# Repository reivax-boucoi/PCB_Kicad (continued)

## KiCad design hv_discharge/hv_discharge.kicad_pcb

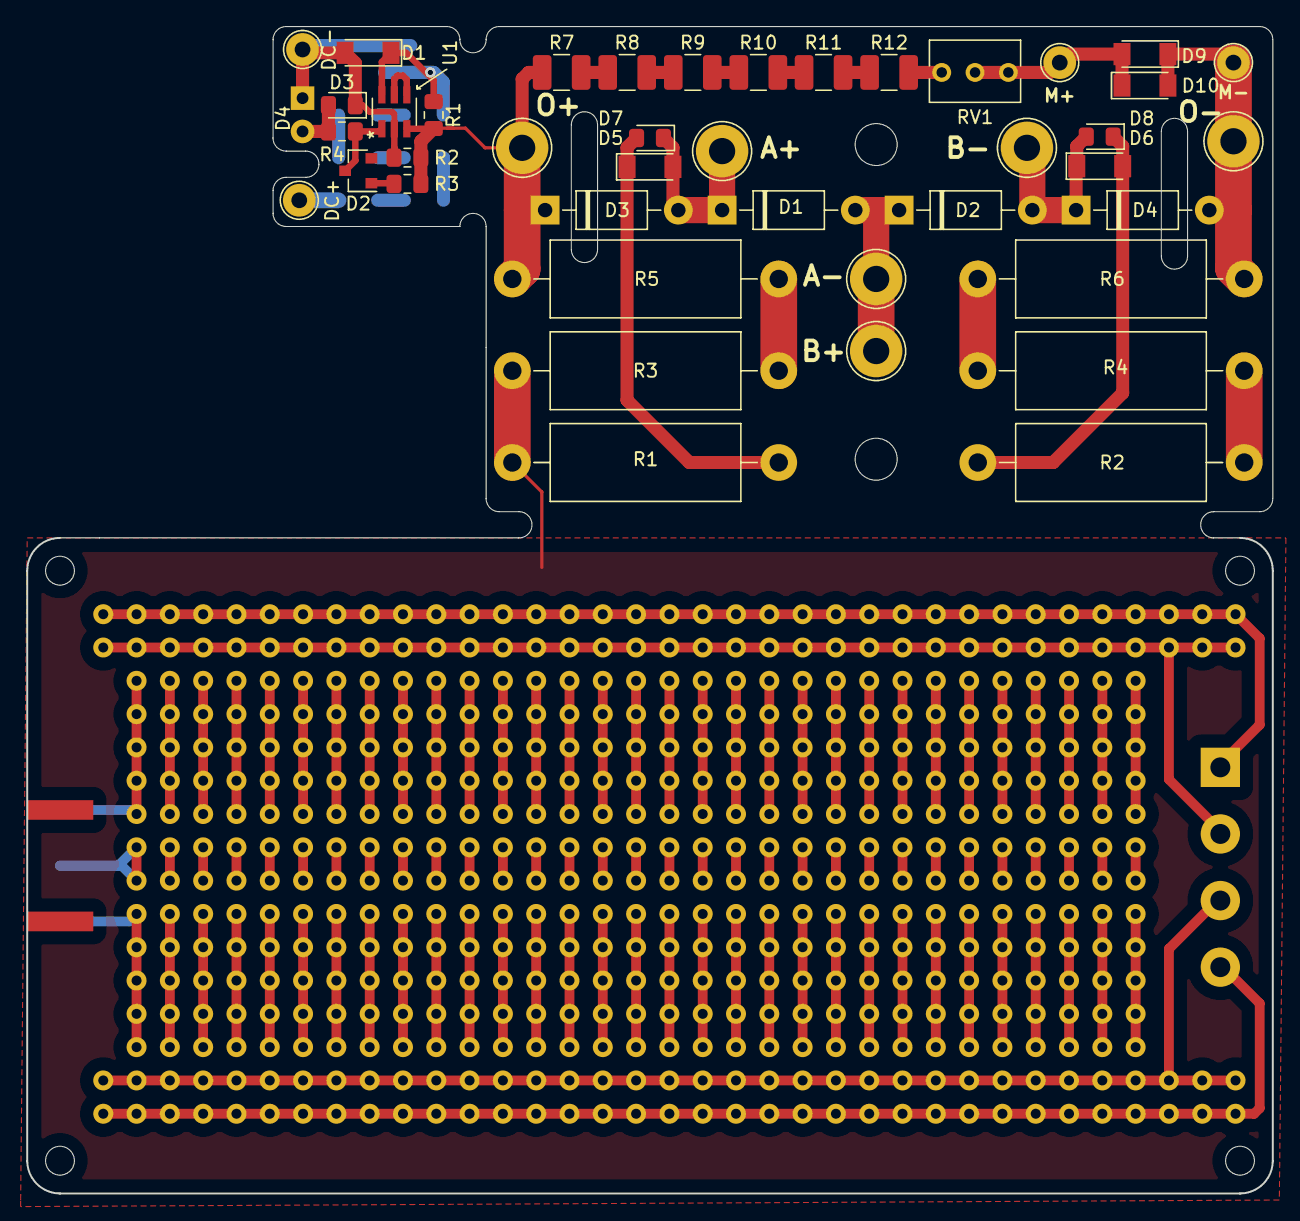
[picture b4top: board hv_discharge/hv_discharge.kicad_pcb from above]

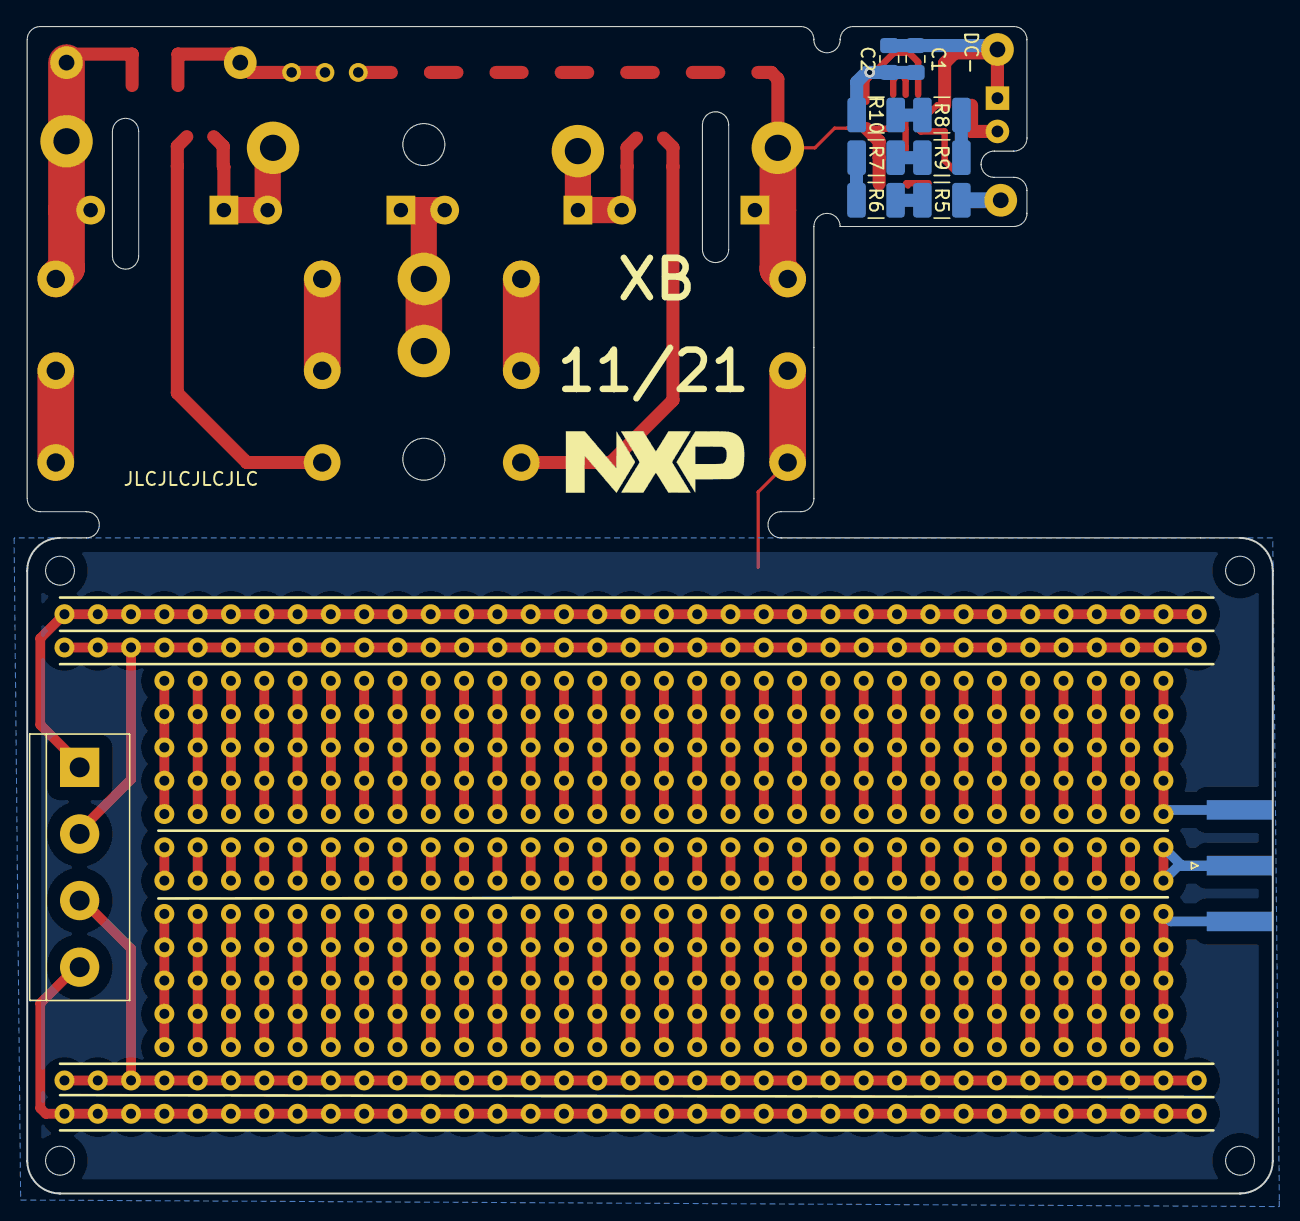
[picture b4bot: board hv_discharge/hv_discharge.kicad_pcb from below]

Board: 2 copper layers, 95.0 x 89.0 mm, 50 parts (8 on the bottom side), 18 nets.

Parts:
C1, C2: 10u; C_0805_2012Metric_Pad1.15x1.40mm_HandSolder
D1: D_Zener; D_MiniMELF
D1#2, D2#2, D3#2, D4#2: 1N4007; D_DO-41_SOD81_P10.16mm_Horizontal
D2: BAT54W; SOT-23
D3, D7, D8: LED; LED_0805_2012Metric_Pad1.15x1.40mm_HandSolder
D4: LED; LED_D5.0mm
D5, D6, D9, D10: D; D_MiniMELF
DC+: DC+; TestPoint_THTPad_D2.5mm_Drill1.2mm
DC-: DC-; TestPoint_THTPad_D2.5mm_Drill1.2mm
J1: B-; TestPoint_THTPad_D4.0mm_Drill2.0mm
J2: A+; TestPoint_THTPad_D4.0mm_Drill2.0mm
J3: B+; TestPoint_THTPad_D4.0mm_Drill2.0mm
J4: A-; TestPoint_THTPad_D4.0mm_Drill2.0mm
J5: M+; TestPoint_THTPad_D2.5mm_Drill1.2mm
J6: M-; TestPoint_THTPad_D2.5mm_Drill1.2mm
J7: O-; TestPoint_THTPad_D4.0mm_Drill2.0mm
J8: O+; TestPoint_THTPad_D4.0mm_Drill2.0mm
R1, R2, R3: 100k; R_0805_2012Metric_Pad1.15x1.40mm_HandSolder
R1#2, R2#2, R5#2, R6#2: 6k8; R_Axial_DIN0614_L14.3mm_D5.7mm_P20.32mm_Horizontal
R3#2, R4#2: 8k2; R_Axial_DIN0614_L14.3mm_D5.7mm_P20.32mm_Horizontal
R4: 1k; R_0805_2012Metric_Pad1.15x1.40mm_HandSolder
R5, R6, R7, R8, R9, R10: 100k; R_1210_3225Metric_Pad1.42x2.65mm_HandSolder
R7#2, R8#2, R9#2, R10#2, R11, R12: 200k; R_1210_3225Metric_Pad1.42x2.65mm_HandSolder
RV1: 200k; Potentiometer_Bourns_3266Y_Vertical
U1: MCP65R41T-2402E_CHY; MCP65R41T-2402E

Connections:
unnamed: D1#2.1, D3#2.2, D5.2, D7.1, J3.1
unnamed: D1#2.2, D2#2.1, J1.1, J2.1
unnamed: D2#2.2, D4#2.1, D6.1, D8.2, J4.1
unnamed: D3#2.1, J8.1, R5#2.1, R7#2.1
unnamed: D5.1, D7.2, R1#2.2
unnamed: D6.2, D8.1, R2#2.1
unnamed: D9.2, D10.1, J5.1, RV1.2, RV1.3
unnamed: D4#2.2, D9.1, D10.2, J6.1, J7.1, R6#2.2
unnamed: R1#2.1, R3#2.2
unnamed: R2#2.2, R4#2.1
unnamed: R3#2.1, R5#2.2
unnamed: R4#2.2, R6#2.1
unnamed: R7#2.2, R8#2.1
unnamed: R8#2.2, R9#2.1
unnamed: R9#2.2, R10#2.1
unnamed: R10#2.2, R11.1
unnamed: R11.2, R12.1
unnamed: R12.2, RV1.1

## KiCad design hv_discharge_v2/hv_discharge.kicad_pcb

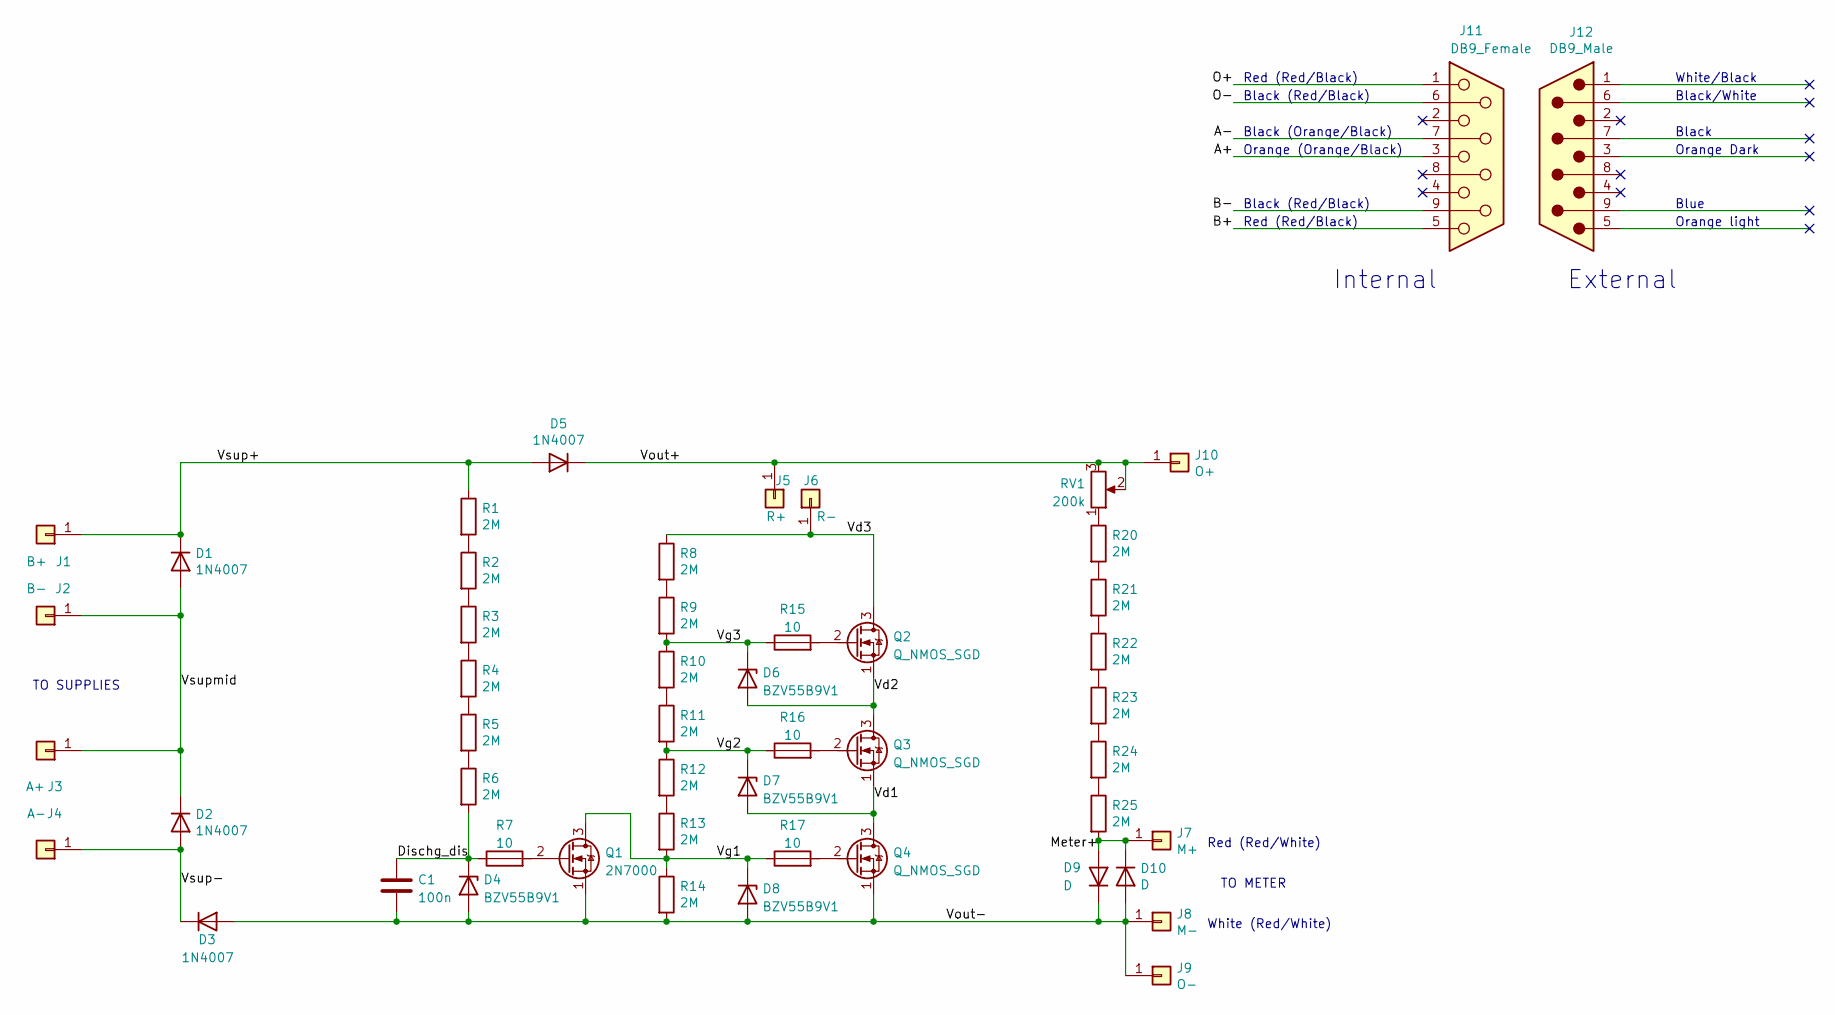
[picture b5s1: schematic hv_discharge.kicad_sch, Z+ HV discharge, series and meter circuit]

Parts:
C1: 100n; C_0805_2012Metric_Pad1.18x1.45mm_HandSolder
D1, D2, D3, D5: 1N4007; D_DO-41_SOD81_P10.16mm_Horizontal
D4, D6, D7, D8: BZV55B9V1; D_MiniMELF
D9, D10: D; D_MiniMELF
J1: B+; TestPoint_THTPad_D4.0mm_Drill2.0mm
J2: B-; TestPoint_THTPad_D4.0mm_Drill2.0mm
J3: A+; TestPoint_THTPad_D4.0mm_Drill2.0mm
J4: A-; TestPoint_THTPad_D4.0mm_Drill2.0mm
J5: R+; TestPoint_THTPad_D4.0mm_Drill2.0mm
J6: R-; TestPoint_THTPad_D4.0mm_Drill2.0mm
J7: M+; TestPoint_THTPad_D2.5mm_Drill1.2mm
J8: M-; TestPoint_THTPad_D2.5mm_Drill1.2mm
J9: O-; TestPoint_THTPad_D4.0mm_Drill2.0mm
J10: O+; TestPoint_THTPad_D4.0mm_Drill2.0mm
J11: DB9_Female
J12: DB9_Male
Q1: 2N7000; TO-92_Inline_Wide
Q2, Q3, Q4: Q_NMOS_SGD; TO-92L_Wide
R1, R2, R3, R4, R5, R6, R8, R9, R10, R11, R12, R13, R14, R20, R21, R22, R23, R24, R25: 2M; R_0805_2012Metric_Pad1.20x1.40mm_HandSolder
R7, R15, R16, R17: 10; RBridged_0805_2012Metric_Pad1.20x1.40mm_HandSolder
RV1: 200k; Potentiometer_Bourns_3266Z_Horizontal

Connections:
/Dischg_dis: C1.1, D4.1 (K), R6.2, R7.1
/Meter+: D9.2 (A), D10.1 (K), J7.1, R25.2
/Vd1: D7.2 (A), Q3.1 (S), Q4.3 (D)
/Vd2: D6.2 (A), Q2.1 (S), Q3.3 (D)
/Vd3: J6.1, Q2.3 (D), R8.1
/Vg1: D8.1 (K), Q1.3 (D), R13.2, R14.1, R17.1
/Vg2: D7.1 (K), R11.2, R12.1, R16.1
/Vg3: D6.1 (K), R9.2, R10.1, R15.1
/Vout+: D5.1 (K), J5.1, J10.1, RV1.2, RV1.3
/Vout-: C1.2, D3.2 (A), D4.2 (A), D8.2 (A), D9.1 (K), D10.2 (A), J8.1, J9.1, Q1.1 (S), Q4.1 (S), R14.2
/Vsup+: D1.1 (K), D5.2 (A), J1.1, R1.1
/Vsup-: D2.2 (A), D3.1 (K), J4.1
/Vsupmid: D1.2 (A), D2.1 (K), J2.1, J3.1
unnamed: Q1.2 (G), R7.2
unnamed: Q2.2 (G), R15.2
unnamed: Q3.2 (G), R16.2
unnamed: Q4.2 (G), R17.2
unnamed: R1.2, R2.1
unnamed: R2.2, R3.1
unnamed: R3.2, R4.1
unnamed: R4.2, R5.1
unnamed: R5.2, R6.1
unnamed: R8.2, R9.1
unnamed: R10.2, R11.1
unnamed: R12.2, R13.1
unnamed: R20.1, RV1.1
unnamed: R20.2, R21.1
unnamed: R21.2, R22.1
unnamed: R22.2, R23.1
unnamed: R23.2, R24.1
unnamed: R24.2, R25.1

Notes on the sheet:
White (Red/White)
TO METER
Black (Red/Black)
Black
Black (Orange/Black)
Black/White
External
Orange (Orange/Black)
Red (Red/White)
Blue
Red (Red/Black)
TO SUPPLIES
Orange Dark
White/Black
Internal
Orange light

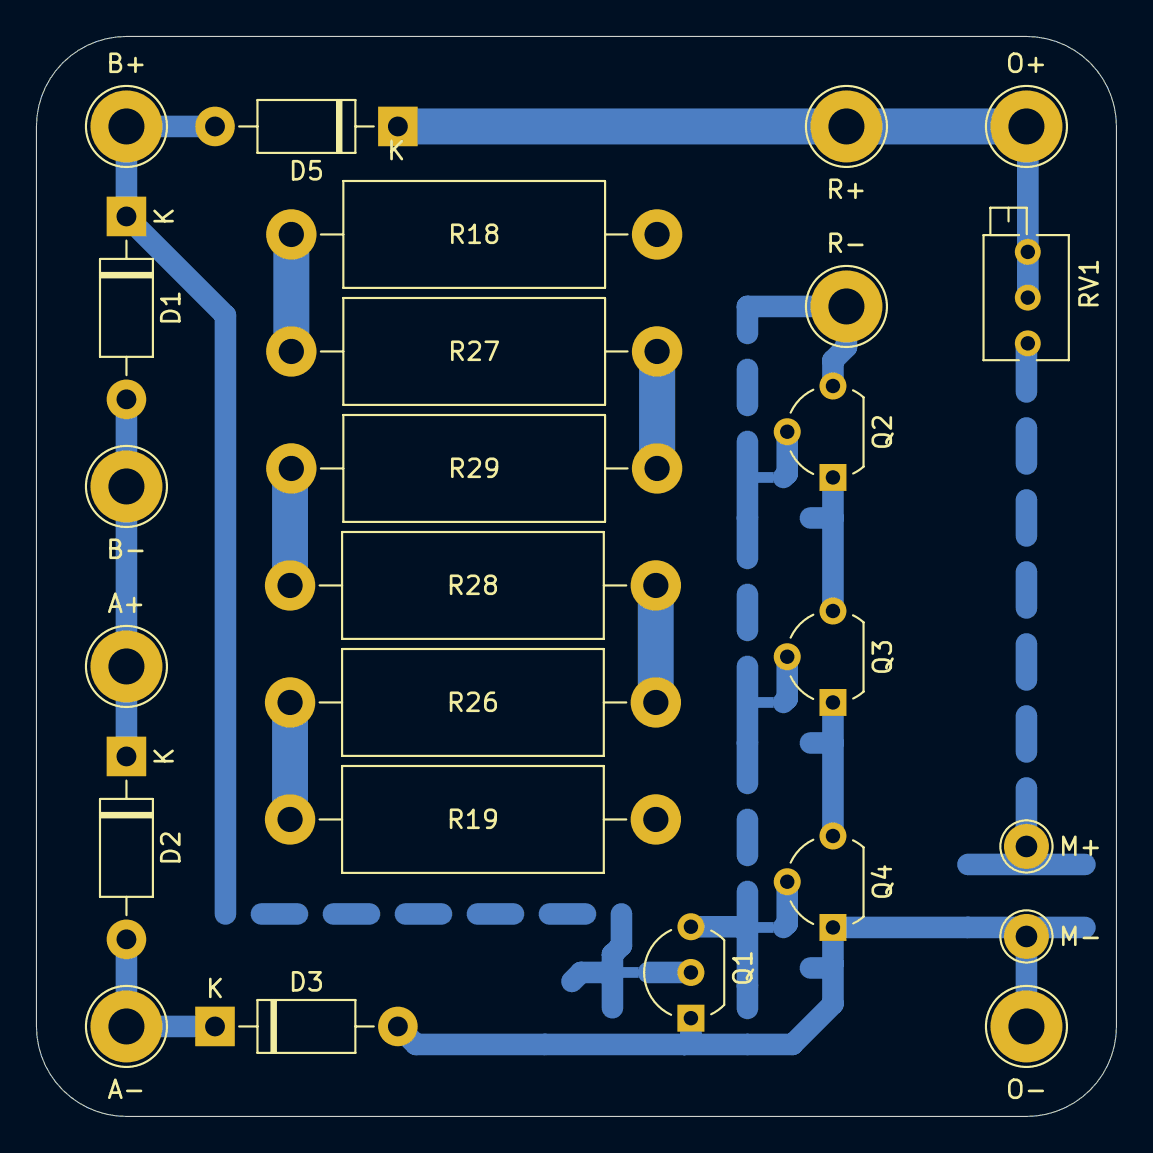
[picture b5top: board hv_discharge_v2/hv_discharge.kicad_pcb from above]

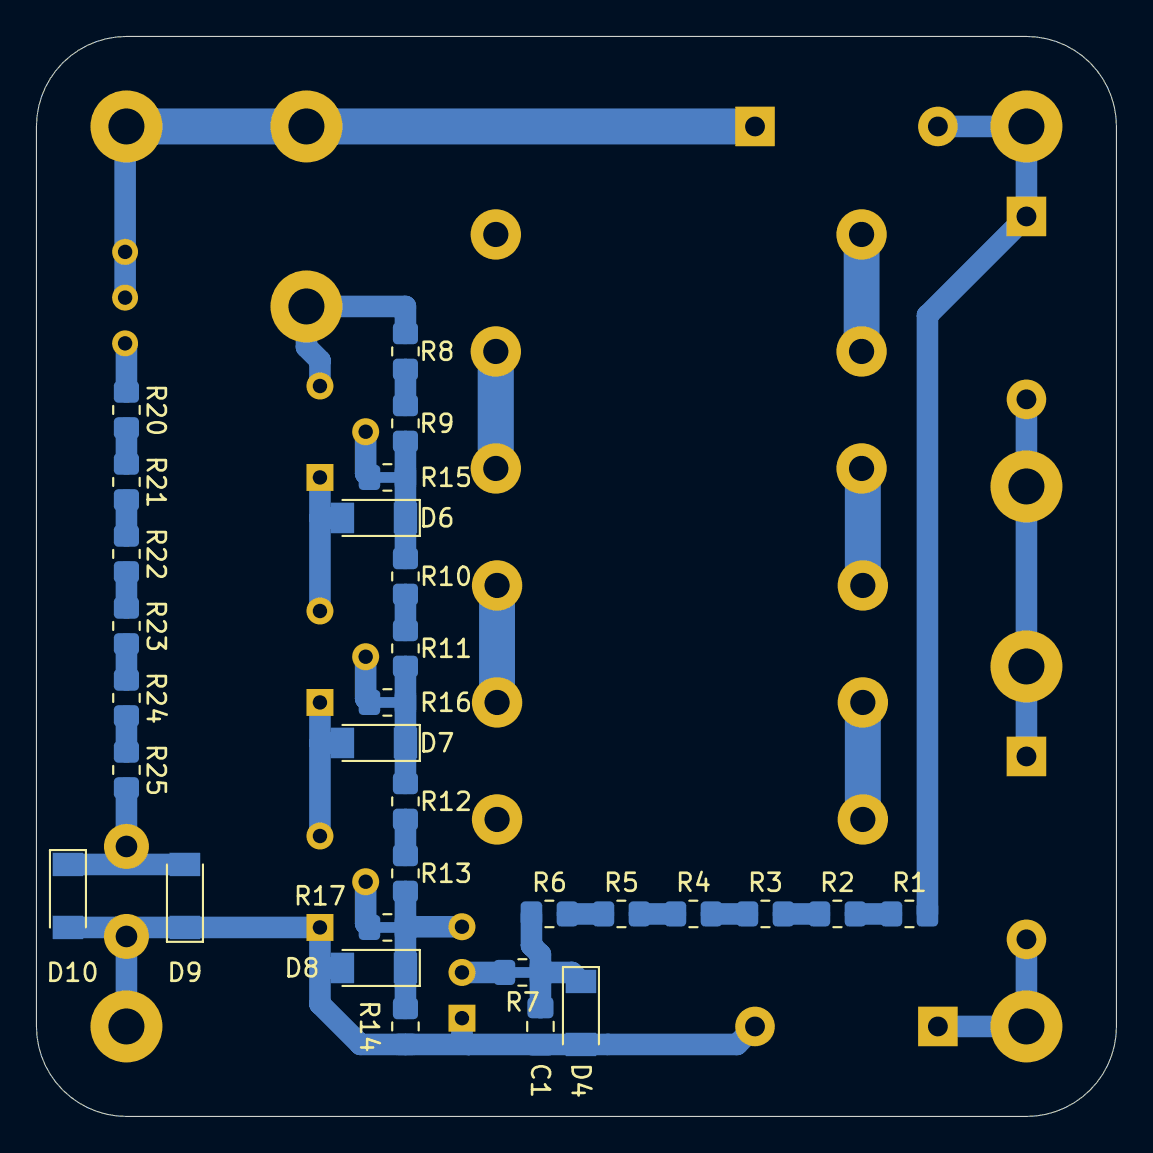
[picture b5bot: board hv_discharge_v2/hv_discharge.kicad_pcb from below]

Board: 2 copper layers, 60.0 x 60.0 mm, 55 parts (30 on the bottom side), 36 nets.

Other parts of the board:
R18, R19, R26, R27, R28, R29: 2k2; R_Axial_DIN0614_L14.3mm_D5.7mm_P20.32mm_Horizontal

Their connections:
unnamed: R18.2, R27.1
unnamed: R19.2, R26.1
unnamed: R26.2, R28.1
unnamed: R27.2, R29.1
unnamed: R28.2, R29.2

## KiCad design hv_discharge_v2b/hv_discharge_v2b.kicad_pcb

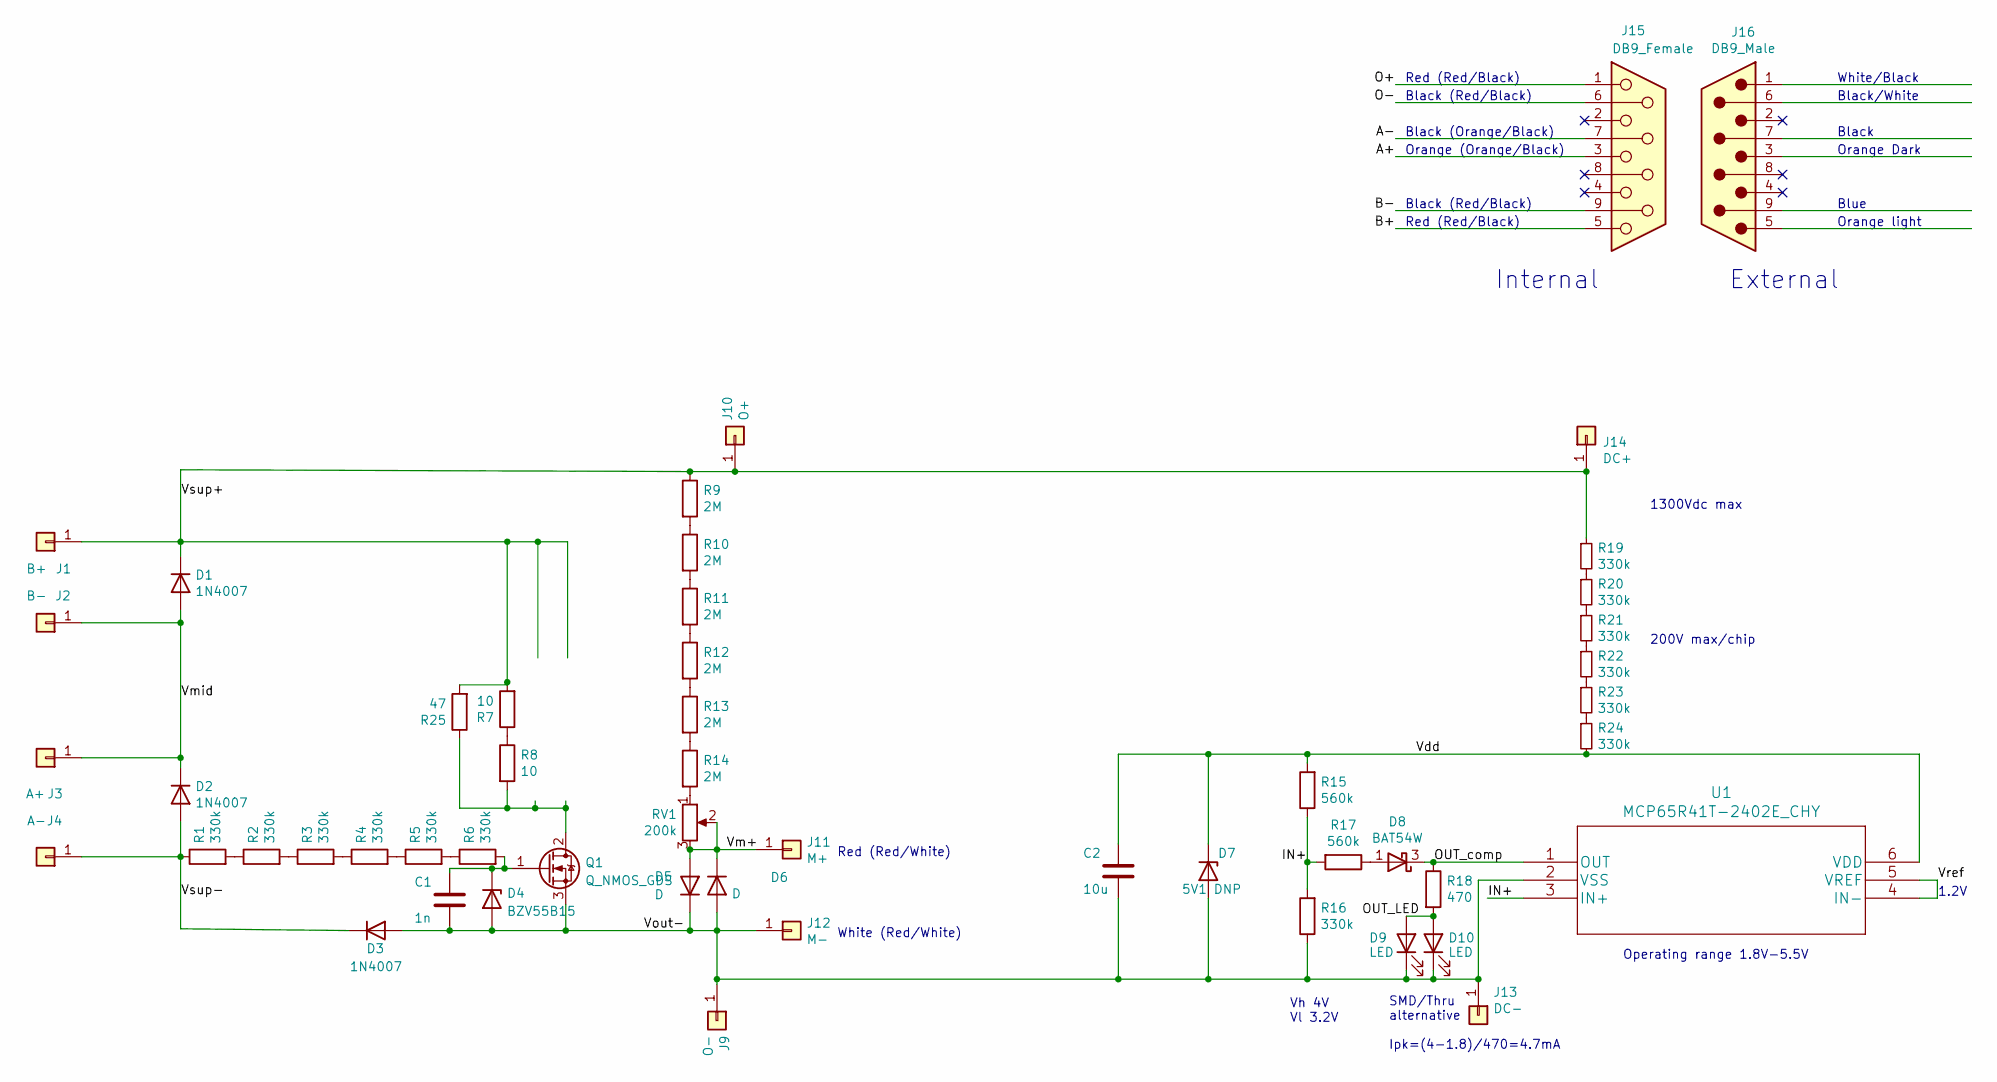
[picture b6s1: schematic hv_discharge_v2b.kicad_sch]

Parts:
C1: 1n; C_0805_2012Metric_Pad1.18x1.45mm_HandSolder
C2: 10u; C_0805_2012Metric_Pad1.18x1.45mm_HandSolder
D1, D2, D3: 1N4007; D_DO-41_SOD81_P10.16mm_Horizontal
D4: BZV55B15; D_MiniMELF
D5, D6: D; D_MiniMELF
D7: 5V1 DNP; D_MiniMELF
D8: BAT54W; SOT-23
D9: LED; LED_0805_2012Metric_Pad1.15x1.40mm_HandSolder
D10: LED; LED_D5.0mm
J1: B+; TestPoint_THTPad_D4.0mm_Drill2.0mm
J2: B-; TestPoint_THTPad_D4.0mm_Drill2.0mm
J3: A+; TestPoint_THTPad_D4.0mm_Drill2.0mm
J4: A-; TestPoint_THTPad_D4.0mm_Drill2.0mm
J9: O-; TestPoint_THTPad_D4.0mm_Drill2.0mm
J10: O+; TestPoint_THTPad_D4.0mm_Drill2.0mm
J11: M+; TestPoint_THTPad_D2.5mm_Drill1.2mm
J12: M-; TestPoint_THTPad_D2.5mm_Drill1.2mm
J13: DC-; TestPoint_THTPad_D2.5mm_Drill1.2mm
J14: DC+; TestPoint_THTPad_D2.5mm_Drill1.2mm
J15: DB9_Female
J16: DB9_Male
Q1: Q_NMOS_GDS; TO-247-3_Horizontal_TabDown
R1, R2, R3, R4, R5, R6, R19, R20, R21, R22, R23, R24: 330k; R_1206_3216Metric_Pad1.30x1.75mm_HandSolder
R7, R8: 10; THS2510RJ
R9, R10, R11, R12, R13, R14: 2M; R_1206_3216Metric_Pad1.30x1.75mm_HandSolder
R15, R17: 560k; R_0805_2012Metric_Pad1.20x1.40mm_HandSolder
R16: 330k; R_0805_2012Metric_Pad1.20x1.40mm_HandSolder
R18: 470; R_0805_2012Metric_Pad1.20x1.40mm_HandSolder
R25: 47; HSC100
RV1: 200k; Potentiometer_Bourns_3266Y_Vertical
U1: MCP65R41T-2402E_CHY; MCP65R41T-2402E

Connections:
/IN+: R15.1, R16.2, R17.2, U1.3 (IN+)
/OUT_LED: D9.2 (A), D10.2 (A), R18.2
/OUT_comp: D8.3 (K), R18.1, U1.1 (OUT)
/Vdd: C2.1, D7.1 (K), R15.2, R24.2, U1.6 (VDD)
/Vm+: D5.2 (A), D6.1 (K), J11.1, RV1.2, RV1.3
/Vmid: D1.2 (A), D2.1 (K), J2.1, J3.1
/Vout-: C1.2, C2.2, D3.2 (A), D4.2 (A), D5.1 (K), D6.2 (A), D7.2 (A), D9.1 (K), D10.1 (K), J9.1, J12.1, J13.1, Q1.3 (S), R16.1, U1.2 (VSS)
/Vref: U1.4 (IN-), U1.5 (VREF)
/Vsup+: D1.1 (K), J1.1, J10.1, J14.1, R7.2, R9.1, R19.1, R25.2
/Vsup-: D2.2 (A), D3.1 (K), J4.1, R1.1
unnamed: C1.1, D4.1 (K), Q1.1 (G), R6.2
unnamed: D8.1 (A), R17.1
unnamed: Q1.2 (D), R8.2, R25.1
unnamed: R1.2, R2.1
unnamed: R2.2, R3.1
unnamed: R3.2, R4.1
unnamed: R4.2, R5.1
unnamed: R5.2, R6.1
unnamed: R7.1, R8.1
unnamed: R9.2, R10.1
unnamed: R10.2, R11.1
unnamed: R11.2, R12.1
unnamed: R12.2, R13.1
unnamed: R13.2, R14.1
unnamed: R14.2, RV1.1
unnamed: R19.2, R20.1
unnamed: R20.2, R21.1
unnamed: R21.2, R22.1
unnamed: R22.2, R23.1
unnamed: R23.2, R24.1

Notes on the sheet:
1.2V
Red (Red/Black)
Black (Orange/Black)
Black (Red/Black)
Orange light
Black
Black/White
Orange (Orange/Black)
White (Red/White)
Blue
200V max/chip
Orange Dark
Red (Red/White)
1300Vdc max
Vh 4V Vl 3.2V
External
Internal
Operating range 1.8V-5.5V
SMD/Thru alternative Ipk=(4-1.8)/470=4.7mA
White/Black

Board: 2 copper layers, 50 parts (31 on the bottom side), 30 nets, no tracks yet.

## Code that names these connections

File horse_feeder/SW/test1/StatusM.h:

#ifndef STATUSM_H
#define STATUSM_H

#include <Arduino.h>
#include <EEPROM.h>
#include "Horaires.h"

#define EEPROM_STATUS_ADDR 80  // EEPROM start address to store status
#define BATT_ADC_GAIN (100.0/1024.0*5*10/(10+39)) //TODO change 5V to actual VCC or better use 1V BG ref
#define BATT_MON PIN_PA0
#define BTN_USR1 PIN_PC3    //blue button
#define BTN_USR2 PIN_PC2    //yellow button
#define LED_B PIN_PA3
#define LED_G PIN_PA4
#define LED_Y PIN_PA5
#define LED_R PIN_PA6

#define LED_REDBUTTON 1
#define LED_BLUEBUTTON 2
#define LED_YELLOWBUTTON 3
#define LED_REDBOARD 0

const uint8_t LEDS_pinMap[4]={LED_B,LED_G,LED_Y,LED_R};
//4th LED is OFF: OK, FASTBLINK = Parsing error

#define ERRORTypeNB 5
#define LED_FASTBLINK_PERIOD 150 //period in ms
#define LED_SLOWBLINK_PERIOD 7 //number of fastblink periods

enum ErrorType {
    SIM_ERROR,
    RTC_ERROR,
    M1_ERROR,
    M2_ERROR,
    M12_ERROR
};
enum LED_STATUS {
    LED_OFF,
    LED_FASTBLINK,
    LED_SLOWBLINK,
    LED_ON
};

class StatusM {
    public:
        StatusM(DateTime now);
        void getReport(char *text_content);
        void resetStats();
        uint16_t update(DateTime now);
        void increaseErrorCnt(ErrorType err);
        void animateLEDs();
        void setLED(uint8_t led, LED_STATUS s);
        uint8_t handleButtons();//returns 0: no buttons, 1: blue pressed, 2: blue depressed, 3: yellow pressed
    private:
        LED_STATUS leds[4];
        unsigned long ledFastTime;
        uint8_t ledSlowTime;
        uint8_t buttonStates;

        uint8_t err_cnt[ERRORTypeNB];
        uint16_t startupTime; //in hours since 2025
        DateTime nowTime;
        uint16_t batt_level; //in 10mV LSB, i.e. 1200 = 12.00V
};


#endif

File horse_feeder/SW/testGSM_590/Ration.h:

#ifndef RATION_H
#define RATION_H

#include <Arduino.h>
#include <EEPROM.h>  // Include EEPROM library

#define LAP_TIMEOUT_MS 2500       // Timeout for 1 lap in ms
#define LAP_MINTIME_MS 200       // Min plausible time for 1 lap in ms
#define EEPROM_RATION_ADDR 0  // EEPROM address to store ration quantity
#define EEPROM_RATIONGain_ADDR 1  // EEPROM address to store ration gain
#define RATION_QTY_DFLT 3           //default ration qty (if blank eeprom contents)
#define RATION_GAIN_DFLT 1          //default ration gain (if blank eeprom contents)
#define MOTOR_SPEED_RAMP 5          //motor acceleration
#define MOTOR_START_SPEED 20        //motor turn ON initial speed
#define MOTOR_MAX_SPEED 255         //motor max allowed speed
#define MOTOR_APPROACH_SPEED (MOTOR_MAX_SPEED/1.5)  //motor speed at last turn before stopping/reversing
#define PROXI_PWR_DELAY 5 //time for proxi sensor powerup before takng any readings

#define PROXI_PWR PIN_PC4
#define MOT_PWM PIN_PD4
#define MOT_DIR PIN_PD5
#define MOT1_PROXI PIN_PD3
#define MOT2_PROXI PIN_PD2

enum RationStatus {
    ONGOING_M1=0,      // Distribution is currently happening 
    ONGOING_M2=1,      // Distribution is currently happening 
    CHANGING_DIR=2,
    COMPLETED=3,    // Distribution completed successfully
    TIMED_OUT_M1=4, // Timeout occurred for Motor1
    TIMED_OUT_M2=5, // Timeout occurred for Motor2
    TIMED_OUT_M12=6  // Timeout occurred for Motor1&2
};

class Ration {
private:
    unsigned long startTime; // Time when distribution starts
    RationStatus status;  // Current distribution status

    static Ration* instance; // Static pointer to access class in ISR
    static void INT1_isr();  // Interrupt Service Routine for Motor2 (INT1)
    bool modeBourrageActive=false;
    void loadRationFromEEPROM(); // Load ration from EEPROM
    void saveRationToEEPROM();   // Save ration to EEPROM
    void saveGainToEEPROM();    //Save gain to EEPROM*/

public:
    Ration(); // Constructor
    ~Ration(); // Destructor
    initialize();//load ration from eeprom
    void setRation(uint16_t qty);  // Set ration quantity
    void setGain(uint16_t g);  // Set ration gain
    void modeBourrage(bool active);
    uint16_t ration_qty;   // Number of INT0/INT1 interrupts before stopping
    uint16_t effective_ration_qty;
    uint16_t ration_gain;   //volume to # of INT scaling factor, can be updated via GAIN?/Gain x
    volatile uint16_t countM1; // Count of interrupts for Motor1
    volatile uint16_t countM2; // Count of interrupts for Motor2
    volatile uint8_t mot_speed;
    volatile uint8_t mot_max_speed;
    
    void startDistribution();   // Start ration distribution
    void stopMotor();
    void stopAll();
    void reverseMotorDir();
    void startMotor(bool dir);
    RationStatus update();      // Check and return current distribution status
};

#endif
